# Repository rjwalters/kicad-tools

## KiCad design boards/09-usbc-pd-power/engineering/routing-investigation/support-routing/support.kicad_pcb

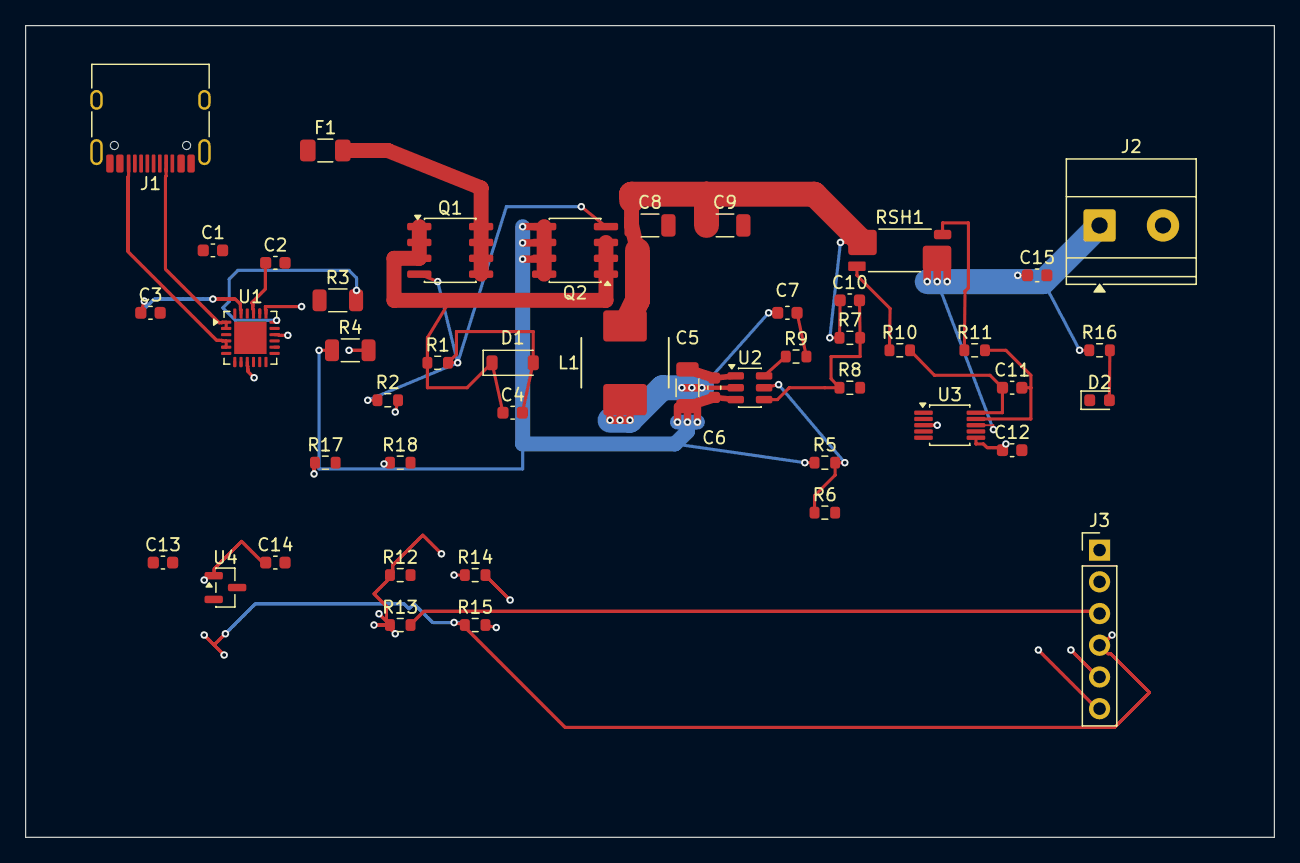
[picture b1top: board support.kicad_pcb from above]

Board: 4 copper layers, 100.0 x 65.0 mm, 47 parts (0 on the bottom side), 32 nets.

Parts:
C1, C13: 1u 50V; C_0603_1608Metric
C2, C3, C14, C15: 1u 16V; C_0603_1608Metric
C4: 4.7n 50V; C_0603_1608Metric
C5: 10u 50V; C_1206_3216Metric
C6, C7, C11, C12: 100n 50V; C_0603_1608Metric
C8, C9: 22u 25V; C_1206_3216Metric
C10: 75p C0G; C_0603_1608Metric
D1: 12V; D_SOD-123
D2: OUTPUT; LED_0603_1608Metric
F1: 2A 32V; Fuse_1206_3216Metric
J1: USB-C PD INPUT; USB_C_Receptacle_HRO_TYPE-C-31-M-12
J2: 5V OUTPUT; TerminalBlock_Phoenix_MKDS-1,5-2-5.08_1x02_P5.08mm_Horizont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
J3: I2C HOST 3V3; PinHeader_1x06_P2.54mm_Vertical
L1: 10uH; SRP7050TA
Q1, Q2: AO4407A; SOIC-8_3.9x4.9mm_P1.27mm
R1, R6: 100k; R_0603_1608Metric
R2, R14, R15, R17, R18: 10k; R_0603_1608Metric
R3, R4: 1k; R_1206_3216Metric
R5: 680k; R_0603_1608Metric
R7: 100k 0.1%; R_0603_1608Metric
R8: 13.3k 0.1%; R_0603_1608Metric
R9: 49.9; R_0603_1608Metric
R10, R11: 10; R_0603_1608Metric
R12, R13: 4.7k; R_0603_1608Metric
R16: 2.2k; R_0603_1608Metric
RSH1: 10m 1% 1W; R_Shunt_Vishay_WSK2512_6332Metric_T1.19mm
U1: STUSB4500QTR; QFN-24-1EP_4x4mm_P0.5mm_EP2.6x2.6mm
U2: TPS54302DDCR; TSOT-23-6
U3: INA226AIDGSR; MSOP-10_3x3mm_P0.5mm
U4: TLV76033DBZR; SOT-23

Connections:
+3V3: C12.1, C14.1, J3.4, R12.1, R13.1, R14.1, R15.1, R17.1, R18.1, U3.6, U4.1
+5V_OUT: C15.1, J2.1, R16.1, RSH1.4, U3.8
BOOT: R9.1, U2.6
BOOT_CAP: C7.1, R9.2
BUCK_EN: R5.2, R6.1, U2.5
CC1: J1.A5, U1.1, U1.2
CC2: J1.B5, U1.4, U1.5
DISCHARGE: R4.2, U1.9
FB: C10.2, R7.2, R8.1, U2.4
GND: C1.2, C2.2, C3.2, C5.2, C6.2, C8.2, C9.2, C12.2, C13.2, C14.2, C15.2, D2.1, J1.A1, J1.A12, J1.B1, J1.B12, J1.SH, J2.2, J3.1, R6.2, R8.2, U1.6, U1.10, U1.12, U1.13, U1.22, U1.25, U2.1, U3.1, U3.2, U3.7, U4.3
KELVIN_N: R11.1, RSH1.3
KELVIN_P: R10.1, RSH1.2
LED_A: D2.2, R16.2
MON_ALERT: J3.6, R15.2, U3.3
PD_ALERT: J3.5, R14.2, U1.19
PD_OK2: R17.2, U1.20
PD_OK3: R18.2, U1.14
PMOS_GATE: C4.2, D1.2, Q1.4, Q2.4, R1.2, R2.1
PMOS_SOURCE: C4.1, D1.1, Q1.1, Q1.2, Q1.3, Q2.1, Q2.2, Q2.3, R1.1
SCL: J3.2, R12.2, U1.7, U3.5
SDA: J3.3, R13.2, U1.8, U3.4
SENSE_N: C11.2, R11.2, U3.9
SENSE_P: C11.1, R10.2, U3.10
SINK_GATE: R2.2, U1.16
SW: C7.2, L1.1, U2.2
VBUS_FUSED: F1.2, Q1.5, Q1.6, Q1.7, Q1.8
VBUS_RAW: C1.1, C13.1, F1.1, J1.A4, J1.A9, J1.B4, J1.B9, R3.1, U1.24, U4.2
VBUS_SENSE: R3.2, U1.18
VIN: C5.1, C6.1, Q2.5, Q2.6, Q2.7, Q2.8, R4.1, R5.1, U2.3
VOUT_PRE: C8.1, C9.1, C10.1, L1.2, R7.1, RSH1.1
VREG_1V2: C2.1, U1.21
VREG_2V7: C3.1, U1.23

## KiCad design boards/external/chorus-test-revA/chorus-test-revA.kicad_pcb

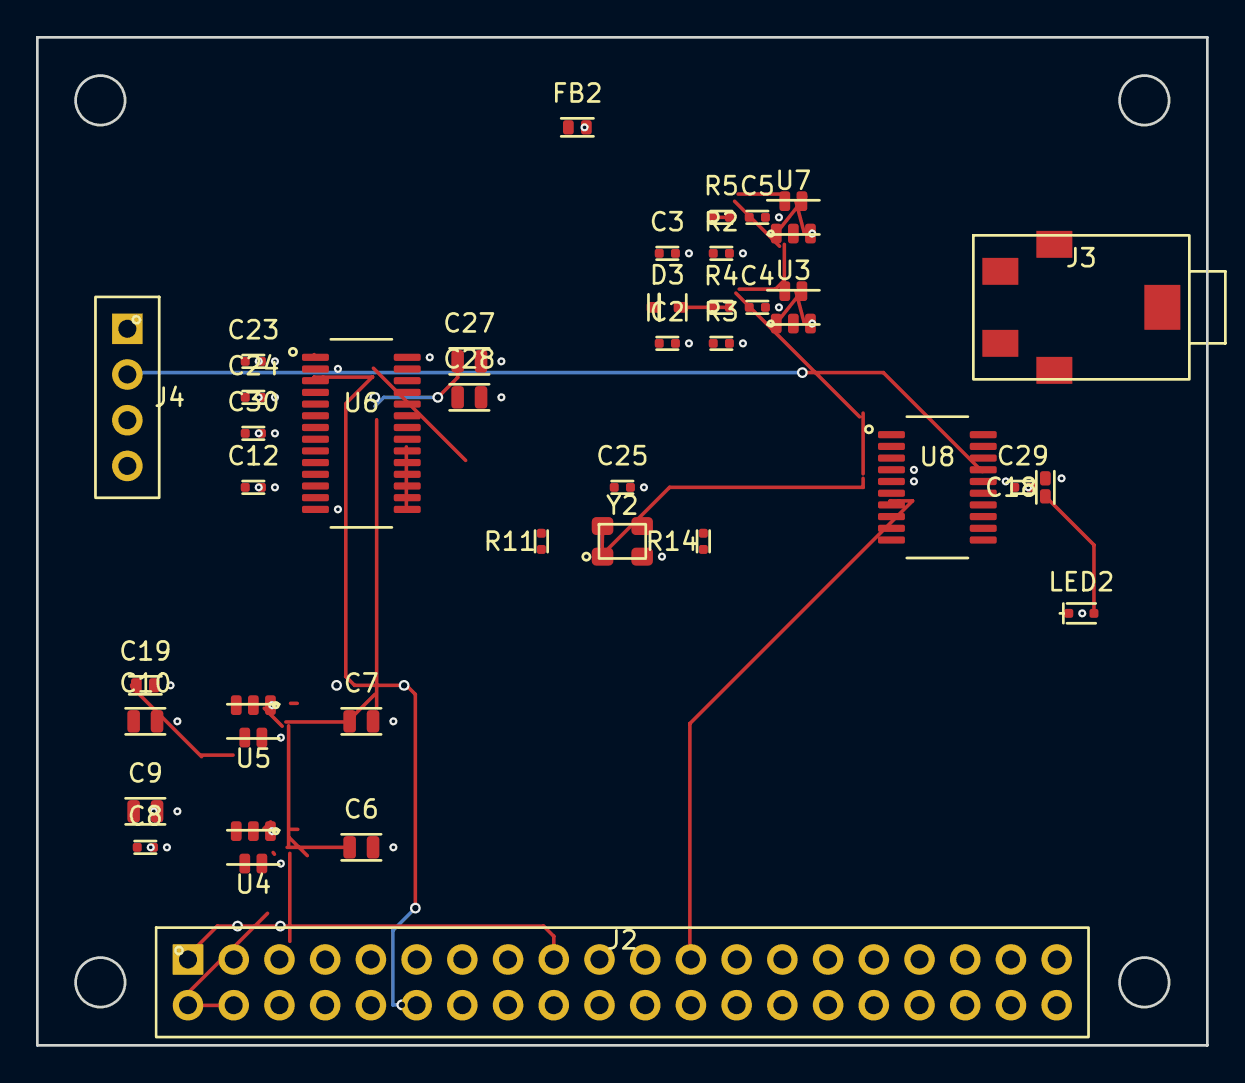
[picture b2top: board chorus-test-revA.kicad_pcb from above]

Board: 4 copper layers, 65.0 x 56.0 mm, 38 parts (0 on the bottom side), 20 nets.

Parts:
C2, C3, C4, C5, C8, C25, C29, C30: 100nF; C_0402_1005Metric
C6, C7, C9, C10, C27, C28: 10uF; C_0805_2012Metric
C12: 100nF 100V; C_0402_1005Metric
C18, C19: 2.2uF 25V; C_0603_1608Metric
C23, C24: 2.2nF 50V; C_0402_1005Metric
D3: BAT54; D_SOD-323
FB2: 470R; L_0603_1608Metric
J2: RPi_GPIO; PinSocket_2x20_P2.54mm
J3: Audio_Out; Jack_3.5mm_Horizontal
J4: SWD; PinHeader_1x04_P2.54mm
LED2: PWR GRN; LED_0603_1608Metric
R2, R3: 100k; R_0402_1005Metric
R4, R5: 10k; R_0402_1005Metric
R11: 30R; R_0402_1005Metric
R14: 33R; R_0402_1005Metric
U3, U7: 74LVC1G17; SOT-23-5
U4, U5: XC6206-3.3V; SOT-23-5
U6: PCM5122PW; TSSOP-28_4.4x9.7mm_P0.65mm
U8: STM32C011F4P6; TSSOP-20_4.4x6.5mm_P0.65mm
Y2: 24.576MHz; Oscillator_SMD_3.2x2.5mm

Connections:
+3.3V: C8.1, C9.1, C12.1, C18.1, C29.1, C30.1, J2.1, J2.17, J4.1, LED2.2, U3.5, U4.5, U6.18, U6.28, U7.5, U8.5, Y2.1, Y2.4
+3.3VA: C10.1, C19.1, C23.1, C24.1, U5.5, U6.1, U6.8
+5V: C6.1, C7.1, C27.1, C28.1, J2.2, J2.4, U4.1, U5.1
AUDIO_L: C2.1, D3.1, J3.T
AUDIO_R: C3.1, J3.R
GND: C2.2, C3.2, C4.2, C5.2, C6.2, C7.2, C8.2, C9.2, C10.2, C12.2, C18.2, C19.2, C23.2, C24.2, C25.2, C27.2, C28.2, C29.2, C30.2, FB2.1, J2.6, J2.9, J2.14, J2.25, J2.39, J4.4, LED2.1, R2.2, R3.2, U3.2, U4.2, U5.2, U6.16, U6.17, U6.24, U6.27, U7.2, U8.4, U8.16, Y2.2
GNDA: FB2.2, J3.S, U6.3, U6.9
I2S_BCLK: J2.12, U6.21
I2S_DIN: J2.38, U6.22
I2S_LRCLK: J2.35, U6.23
MCLK: C25.1, R11.1, R14.1, Y2.3
MCLK_DAC: R11.2, U6.20
MCLK_MCU: R14.2, U8.15
SPI_MISO: J2.21, U8.8
SPI_MOSI: J2.19, U8.9
SPI_SCK: J2.23, U8.7
SWCLK: J4.3, U8.18
SWDIO: J4.2, U8.17
SYNC_L: C4.1, D3.2, R3.1, R4.1, R4.2, U3.1, U3.3, U3.4
SYNC_R: C5.1, R2.1, R5.1, R5.2, U7.1, U7.3, U7.4

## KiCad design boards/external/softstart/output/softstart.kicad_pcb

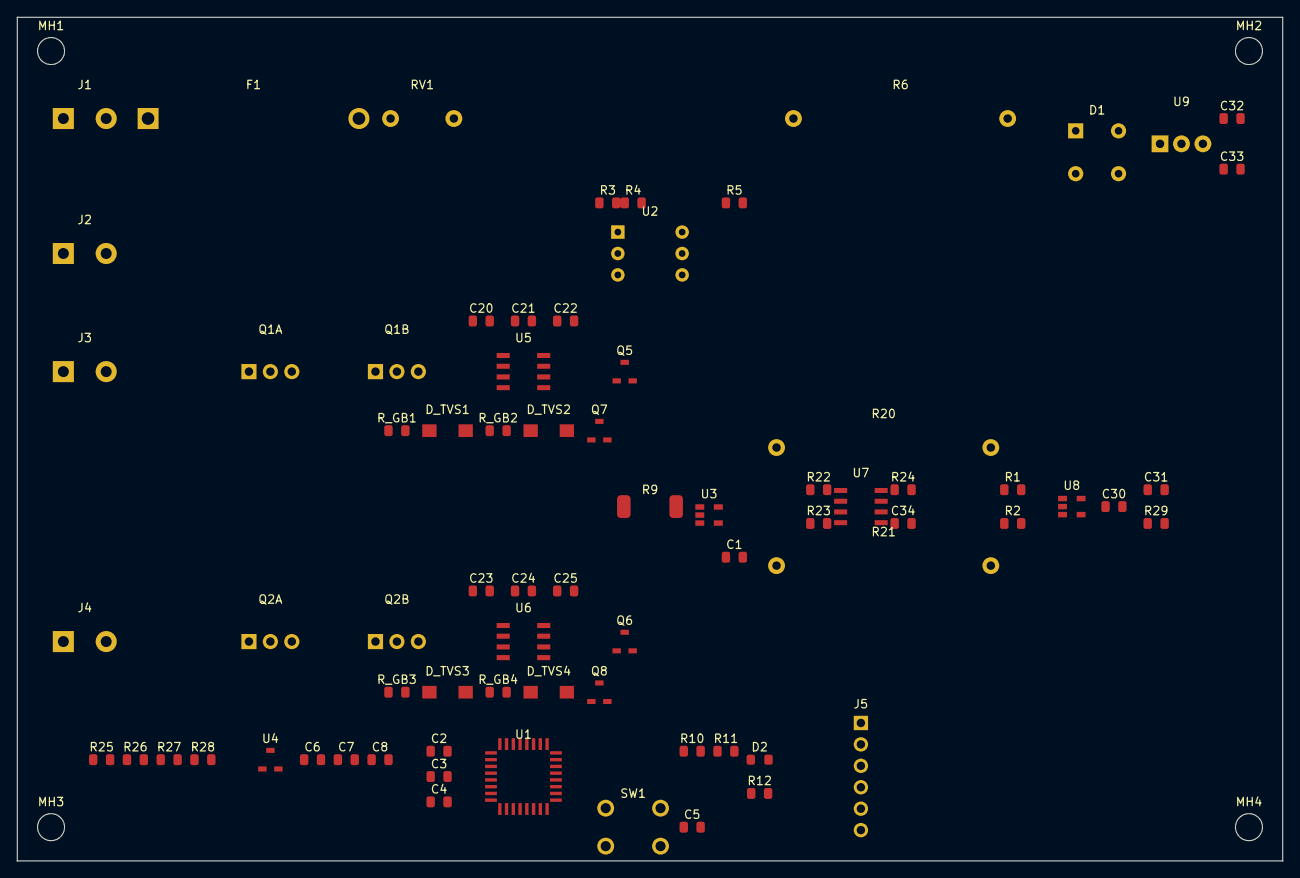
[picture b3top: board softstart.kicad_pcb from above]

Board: 2 copper layers, 150.0 x 100.0 mm, 78 parts (0 on the bottom side), 39 nets, no tracks yet.

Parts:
C1, C2, C3, C5, C8, C20, C22, C23, C25, C30, C31, C33, C34: 100nF; C_0805_2012Metric
C4: 4.7uF; C_0805_2012Metric
C6, C7, C21, C24, C32: 10uF; C_0805_2012Metric
D1: DB107; Diode_Bridge_DIP-4_W7.62mm_P5.08mm
D2: LED; LED_0805_2012Metric
D_TVS1, D_TVS2, D_TVS3, D_TVS4: SMBJ18A; D_SMA
F1: 15A; Fuseholder_Cylinder-5x20mm_Schurter_0031.8201_Horizontal_Op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
J1, J2, J3, J4: TB; TerminalBlock_bornier-2_P5.08mm
J5: SWD; PinHeader_1x06_P2.54mm_Vertical
MH1, MH2, MH3, MH4: MountingHole; MountingHole_3.2mm_M3
Q1A, Q1B, Q2A, Q2B: IRFB4110; TO-220-3_Vertical
Q5, Q6: AO3400; SOT-23
Q7, Q8: 2N7002; SOT-23
R1: 1M; R_0805_2012Metric
R2, R5, R10, R11, R23, R24, R29: 10k; R_0805_2012Metric
R3, R4: 33k; R_0805_2012Metric
R6: 150R 5W; R_Axial_DIN0617_L17.0mm_D6.0mm_P25.40mm_Horizontal
R9: 5mR; R_2512_6332Metric
R12, R22: 1k; R_0805_2012Metric
R20, R21: 100R 5W; R_Axial_DIN0617_L17.0mm_D6.0mm_P25.40mm_Horizontal
R25, R27: 270k; R_0805_2012Metric
R26, R28: 9.1k; R_0805_2012Metric
RV1: 275VAC; RV_Disc_D12mm_W4.2mm_P7.5mm
R_GB1, R_GB2, R_GB3, R_GB4: 10k; R_0805_2012Metric
SW1: RESET; SW_PUSH_6mm
U1: STM32G031K8T6; LQFP-32_7x7mm_P0.8mm
U2: H11AA1; DIP-6_W7.62mm
U3: INA180A3; SOT-23-5
U4: XC6206-3.3V; SOT-23
U5, U6: UCC27211; SOIC-8_3.9x4.9mm_P1.27mm
U7: LM393; SOIC-8_3.9x4.9mm_P1.27mm
U8: MCP6001; SOT-23-5
U9: LM7812; TO-220-3_Vertical

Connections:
+3.3V: C1.1, C2.1, C3.1, C4.1, C7.1, C8.1, C30.1, C34.1, J5.1, Q7.1, Q8.1, R5.1, R10.1, R12.1, R22.1, R24.1, U1.4, U2.6, U3.5, U4.3, U7.8, U8.5
AC_LINE: F1.1, J1.1, R1.1, R3.1, U2.1
AC_NEUTRAL: D1.3, J1.2, J2.2, R4.1, RV1.2, U2.2
BUS_LINE: Q1B.2, Q2B.2, Q5.3, Q6.3, R20.2, R21.2
FUSED_LINE: D1.1, F1.2, J2.1, R6.1, RV1.1
GATE_NEG_A: U1.29, U6.8
GATE_NEG_B: U1.30, U6.7
GATE_POS_A: U1.27, U5.8
GATE_POS_B: U1.28, U5.7
GND: C1.2, C2.2, C3.2, C4.2, C5.2, C6.2, C7.2, C8.2, C30.2, C32.2, C33.2, C34.2, D1.4, D2.2, J5.3, J5.5, R2.2, R11.1, R23.2, R26.2, R28.2, R29.2, SW1.3, SW1.4, U1.5, U2.4, U3.2, U4.2, U7.4, U8.2, U9.2
ISENSE_NEG: R9.2, U3.3
ISENSE_POS: R9.1, U3.1
I_SENSE_OUT: U1.9, U3.4, U7.3
NRST: C5.1, J5.6, Q7.2, Q8.2, R10.2, SW1.1, SW1.2, U1.6
OC_TRIP: R24.2, U1.12, U7.1
PRECHARGE_NEG: Q6.1, U1.32
PRECHARGE_POS: Q5.1, U1.31
SCAP_NEG+: J4.1, Q2A.2, R21.1, R27.1
SCAP_POS+: J3.1, Q1A.2, R20.1, R25.1
SRC_NEG: C23.2, C24.2, C25.2, D_TVS3.2, D_TVS4.2, Q2A.3, Q2B.3, Q6.2, R_GB3.2, R_GB4.2, U6.4, U6.6
SRC_POS: C20.2, C21.2, C22.2, D_TVS1.2, D_TVS2.2, Q1A.3, Q1B.3, Q5.2, R_GB1.2, R_GB2.2, U5.4, U5.6
STATUS_LED: D2.1, R12.2, U1.26
SWCLK: J5.4, R11.2, U1.25
SWDIO: J5.2, U1.24
UCC_HO_NEG: D_TVS3.1, Q2A.1, Q8.3, R_GB3.1, U6.3
UCC_HO_POS: D_TVS1.1, Q1A.1, Q7.3, R_GB1.1, U5.3
UCC_LO_NEG: D_TVS4.1, Q2B.1, R_GB4.1, U6.5
UCC_LO_POS: D_TVS2.1, Q1B.1, R_GB2.1, U5.5
VBOOT_NEG: C23.1, U6.2
VBOOT_POS: C20.1, U5.2
VGATE: C21.1, C22.1, C24.1, C25.1, C33.1, U5.1, U6.1, U9.3
VRECT: C6.1, C32.1, D1.2, U4.1, U9.1
V_AC_SENSE: U1.7, U8.1, U8.4
V_AC_SENSE_RAW: C31.1, R1.2, R2.1, U8.3
V_BANK_NEG_SENSE: R27.2, R28.1, U1.11
V_BANK_POS_SENSE: R25.2, R26.1, U1.10
V_BUS_DVDT: C31.2, R29.1, U1.8
V_OC_TH: R22.2, R23.1, U7.2
ZC_DETECT: R5.2, U1.13, U2.5

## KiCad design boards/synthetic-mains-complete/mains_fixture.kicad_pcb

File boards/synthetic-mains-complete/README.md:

# Synthetic mains-style fixture for `--complete` creepage verification (#8422)

Fully synthetic and public-safe: generated by `generate_fixture.py` with no inputs,
not derived from any real or side-project design.

- `mains_fixture.kicad_pcb`: 2-layer 70x52 mm board. Three mains footprints (`/LINE`,
  `/FUSED_LINE`, `/NEUT`, 150 V class) form a column "wall"; adjacent footprints' pads
  are 2.42 mm apart, so a trace squeezed between them gets ~1.1 mm to each side against
  the 1.6 mm class (IEC 60664-1, PD2, IIIa). Low-voltage links (`/SENSE_A..D`, `GND`)
  between parts either side of the wall take the short path through those gaps unless
  creepage stops them.
- `voltage_map.json`, `net_class_map.json`: the maps passed to both `kct route` and
  `kct creepage`.
- `negotiated_stage.kicad_pcb`: output of the negotiated stage (HV nets + `/SENSE_D`),
  checked in so the regression test (`tests/test_route_complete_creepage_fixture_8422.py`)
  only has to run `--complete`.
- `edge_fixture.kicad_pcb` (generated by `generate_fixture.py --edge`, #9685): the
  board-edge companion. Two 2-pin TH parts one pad-row below the top `Edge.Cuts` line;
  the `/LINE` pads' own copper clears the 1.6 mm 150 V board-edge class by 0.05 mm while
  the 2.0 mm-wide HV track that closes the `/LINE` link reaches 1.4 mm from the edge.
  A router with no copper-vs-board-edge model commits that track and exits 0; the census
  fails `/LINE vs <board edge>` on the same map.
- `edge_net_class_map.json`: gives `/LINE` the 2.0 mm `trace_width` that makes the
  committed track edge-violating while the pads stay clean.

## Recipe

```bash
HV="--net-class-map net_class_map.json --voltage-map voltage_map.json \
    --creepage-standard iec60664 --pollution-degree 2 --material-group IIIa \
    --hv-threshold 0 --skip-drc --no-auto-pour"
kct route mains_fixture.kicad_pcb -o neg.kicad_pcb $HV --nets /LINE,/FUSED_LINE,/NEUT,/SENSE_D
kct route neg.kicad_pcb -o comp.kicad_pcb $HV --complete --complete-report report.json
kct creepage <pcb> --net-class-map net_class_map.json --voltage-map voltage_map.json \
    --standard iec60664 --pollution-degree 2 --material-group IIIa \
    --waive-same-footprint --waive-attach-zone
```

## `--waive-attach-zone` in the replay census (#9717)

`kct route --voltage-map` applies the #4506 rated-footprint attach zones
unconditionally: copper inside a zone is exempt from its post-route HV audit,
and the completion output says so — an `Attach-zone exemption: ENABLED` note
naming `kct creepage --waive-attach-zone` as the way to match that aspect of
the audit. The census side of the exemption is opt-in:

- **Flag omitted (stricter):** every pair whose gap lies inside an attach zone
  is scored on its raw clearance/creepage, so a written board the route gate
  passed can census FAIL. That is not a routing defect — it is the census
  refusing an exemption it was not asked to grant.
- **Flag given:** a pair is waived only when its binding gap lies inside the
  zone AND the residual — the pair re-measured with the zone's copper clipped
  away — still clears the requirement. A failing residual keeps the row FAIL,
  so the flag cannot wave through copper that leaves the zone and creeps
  (#8277's regression pins exactly that case: a trace skimming a rated pad's
  zone edge is reported, not waived).

## Recorded run

Tools: kicad-tools 0.28.0 at `995b75b9d`, Python 3.12.3, C++ router backend built,
linux x86_64, 2026-11-07.

| board | creepage pairs | failing | min creepage (mm) |
|---|---:|---:|---:|
| `mains_fixture` (input) | 22 | 0 | 2.42 |
| after negotiated route | 21 | 0 | 2.00 |
| after `--complete`, **rollback disabled** (counterfactual) | 21 | **6** | **0.253** |
| after `--complete`, as shipped | 21 | **0** | 2.00 |

With the rollback disabled the lattice completion commits 6 failing pairs (e.g.
`/FUSED_LINE`-`GND` 0.253 mm, `/LINE`-`/SENSE_C` 0.300 mm, `/FUSED_LINE`-`/SENSE_B`
0.720 mm, all against 1.6 mm). As shipped, `--complete` rolls back all 5 links that would
have added them (`reason: creepage-rolled-back`, listed in `--complete-report` with
blocking net, required and measured mm) and leaves 0 new failures.

This is harder than #8403's test: that test hand-places one segment on a stub router;
this runs the real negotiated route then the real `--complete` over multiple nets and
both layers, with the census as referee.

## Edge-fixture recipe (#9685)

```bash
EDGE="--net-class-map edge_net_class_map.json --voltage-map voltage_map.json \
    --creepage-standard iec60664 --pollution-degree 2 --material-group IIIa \
    --hv-threshold 0 --skip-drc --no-auto-pour"
kct route edge_fixture.kicad_pcb -o edge_comp.kicad_pcb $EDGE --complete --complete-report edge_report.json
kct creepage <pcb> --net-class-map edge_net_class_map.json --voltage-map voltage_map.json \
    --standard iec60664 --pollution-degree 2 --material-group IIIa --waive-same-footprint
```

As shipped the `/LINE` link is rolled back (`creepage-rolled-back`, blocking net
`<board edge>`, 1.400 mm < required 1.600 mm), the run exits non-zero, and the output
board passes the census including its `/LINE | <board edge>` row (1.65 mm, pads only).
With the rollback disabled (counterfactual, `tests/...8422.py::test_edge_fixture_has_teeth_...`)
the output fails that row at 1.4 mm.

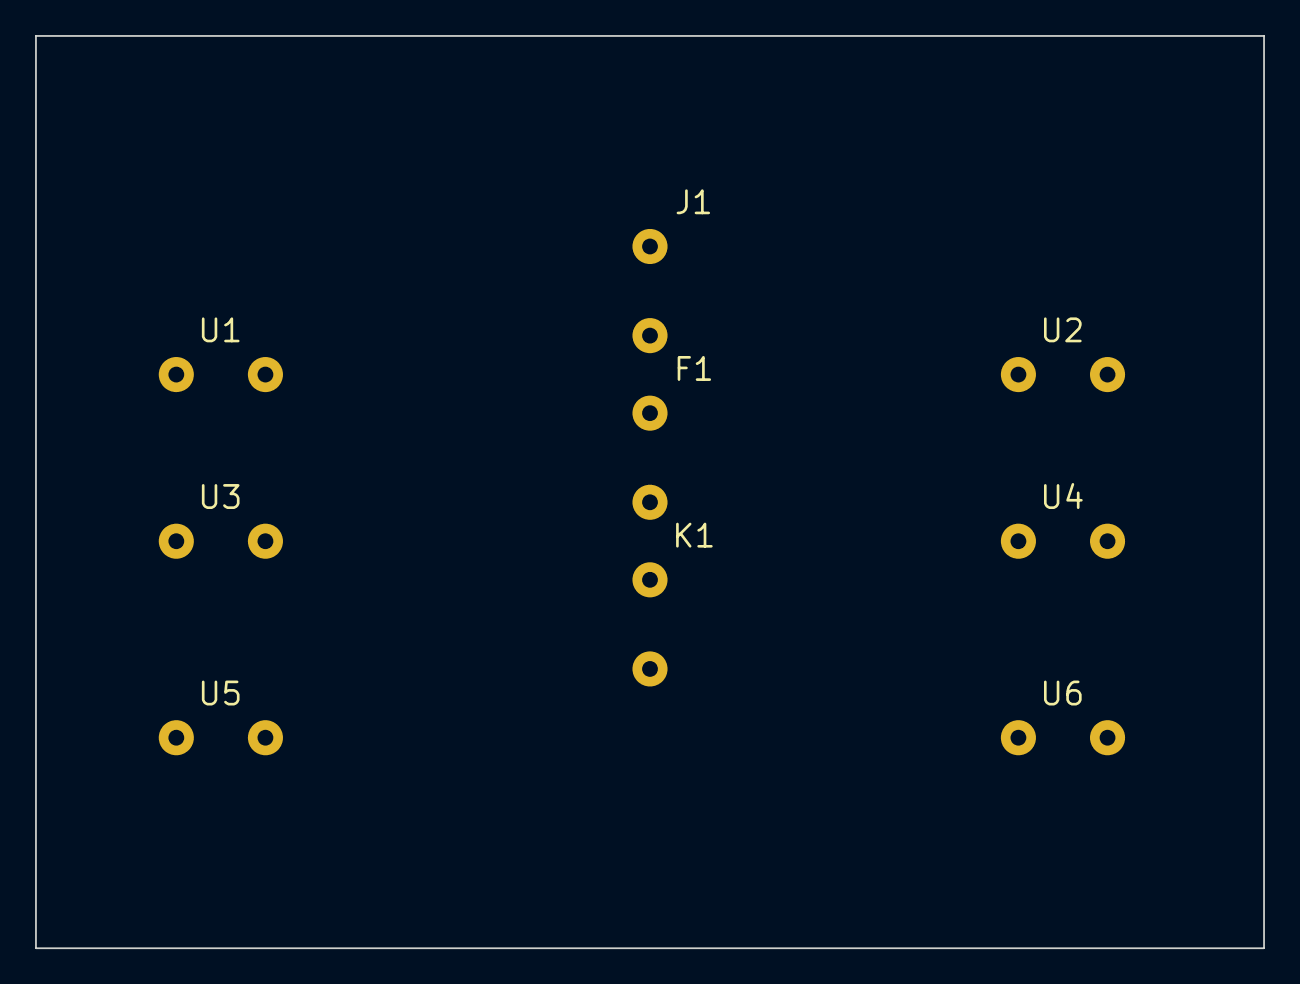
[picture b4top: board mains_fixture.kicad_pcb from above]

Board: 2 copper layers, 70.0 x 52.0 mm, 9 parts (0 on the bottom side), 8 nets, no tracks yet.

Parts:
F1: syn; TH2_F1
J1: syn; TH2_J1
K1: syn; TH2_K1
U1: syn; TH2_U1
U2: syn; TH2_U2
U3: syn; TH2_U3
U4: syn; TH2_U4
U5: syn; TH2_U5
U6: syn; TH2_U6

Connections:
/FUSED_LINE: F1.1, K1.2
/LINE: J1.1, K1.1
/NEUT: F1.2, J1.2
/SENSE_A: U1.1, U2.1
/SENSE_B: U3.1, U4.1
/SENSE_C: U3.2, U4.2
/SENSE_D: U5.1, U6.1
GND: U1.2, U2.2, U5.2, U6.2
